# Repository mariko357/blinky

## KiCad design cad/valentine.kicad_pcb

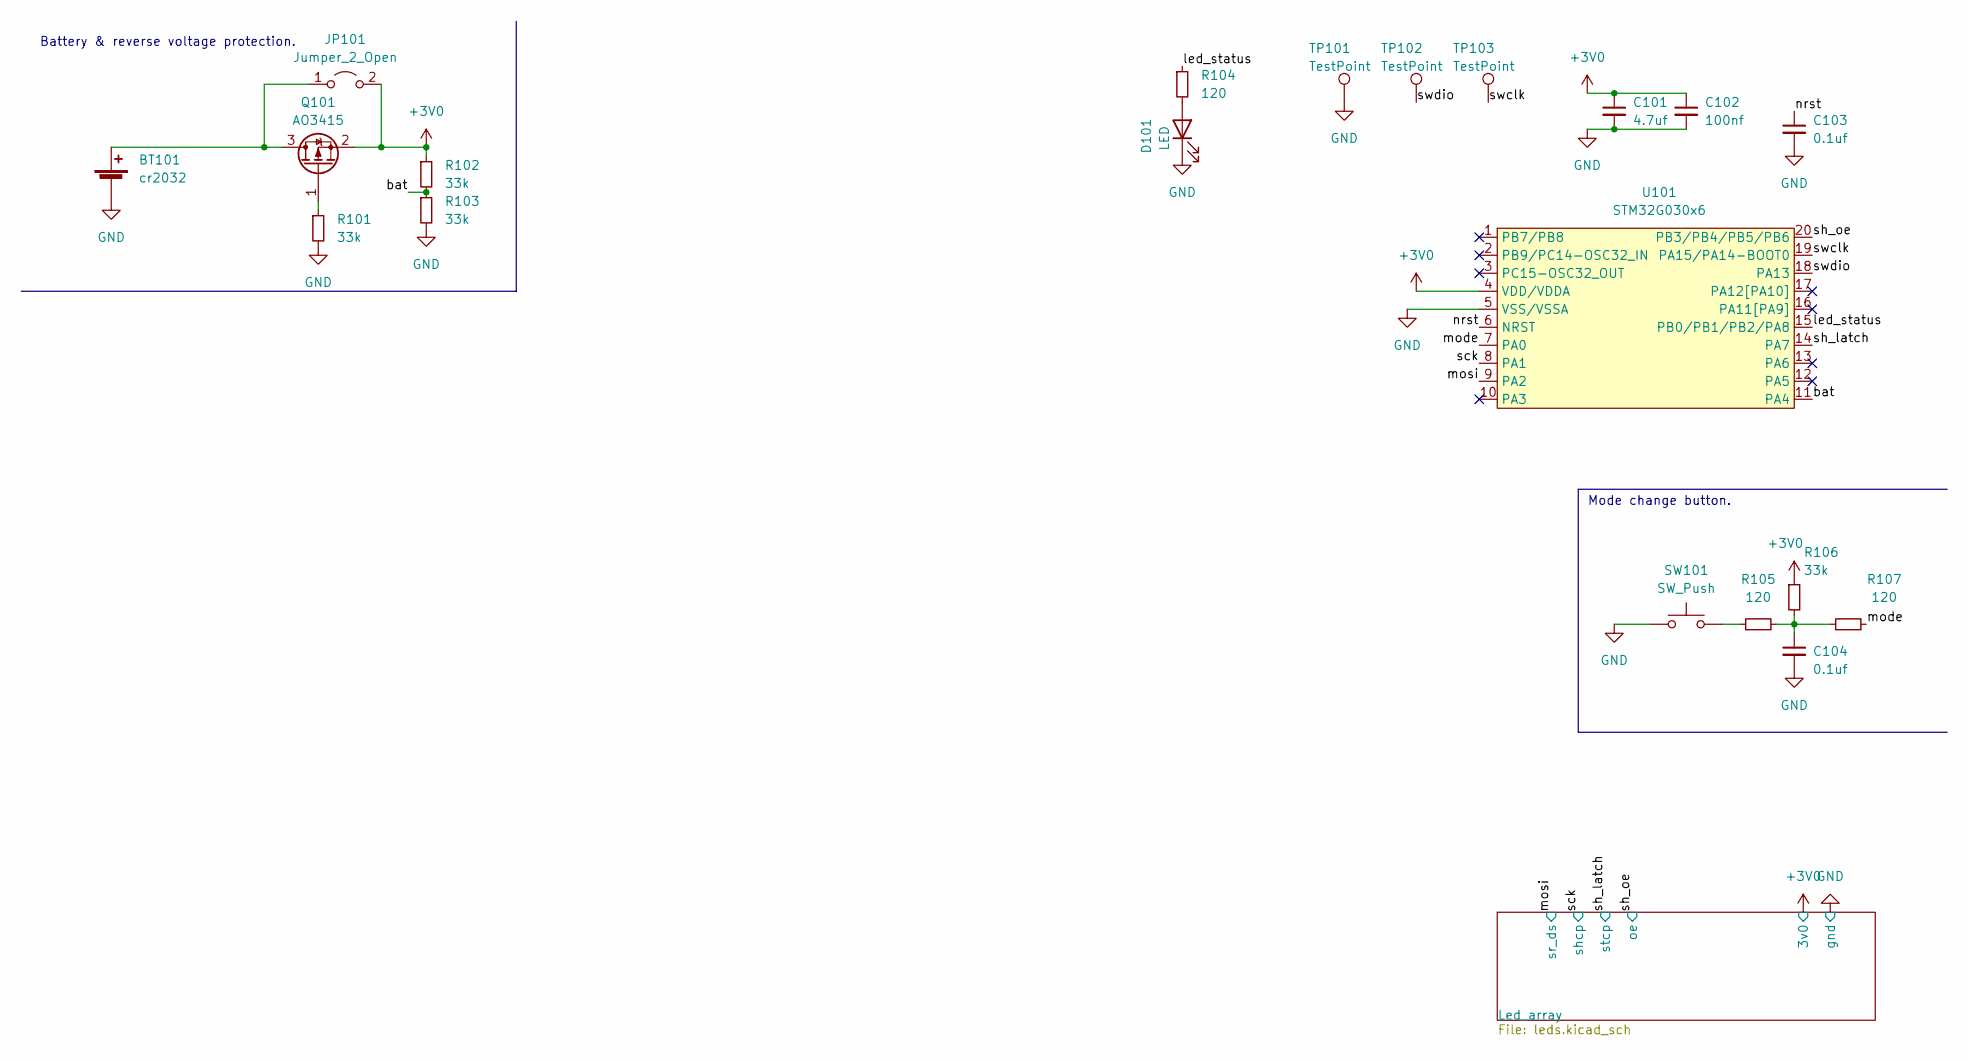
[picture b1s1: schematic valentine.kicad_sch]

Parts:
BT101: cr2032; BatteryHolder_Keystone_3002_1x2032
C101: 4.7uf; C_0603_1608Metric
C102: 100nf; C_0603_1608Metric
C103, C104: 0.1uf; C_0603_1608Metric
D101: LED; LED_0603_1608Metric
JP101: Jumper_2_Open; SolderJumper-2_P1.3mm_Open_TrianglePad1.0x1.5mm
Q101: AO3415; SOT-23
R101, R102, R103, R106: 33k; R_0603_1608Metric
R104, R105, R107: 120; R_0603_1608Metric
SW101: SW_Push; SW_SPST_TL3342
TP101, TP102, TP103: TestPoint; TestPoint_Pad_D1.5mm
U101: STM32G030x6; TSSOP-20_4.4x6.5mm_P0.65mm

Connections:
+3V0: C101.1, C102.1, JP101.2 (B), Q101.2 (S), R102.1, R106.1, U101.4 (VDD/VDDA); also elsewhere on the board
/bat: R102.2, R103.1, U101.11 (PA4)
/led_status: R104.1, U101.15 (PB0/PB1/PB2/PA8)
/mode: R107.2, U101.7 (PA0)
/mosi: U101.9 (PA2); also elsewhere on the board
/nrst: C103.1, U101.6 (NRST)
/sck: U101.8 (PA1); also elsewhere on the board
/sh_latch: U101.14 (PA7); also elsewhere on the board
/sh_oe: U101.20 (PB3/PB4/PB5/PB6); also elsewhere on the board
/swclk: TP103.1, U101.19 (PA15/PA14-BOOT0)
/swdio: TP102.1, U101.18 (PA13)
GND: BT101.2 (-), C101.2, C102.2, C103.2, C104.2, D101.1 (K), R101.2, R103.2, SW101.1, TP101.1, U101.5 (VSS/VSSA); also elsewhere on the board
unnamed: BT101.1 (+), JP101.1 (A), Q101.3 (D)
unnamed: C104.1, R105.2, R106.2, R107.1
unnamed: D101.2 (A), R104.2
unnamed: Q101.1 (G), R101.1
unnamed: R105.1, SW101.2

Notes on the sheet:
Battery & reverse voltage protection.
Mode change button.

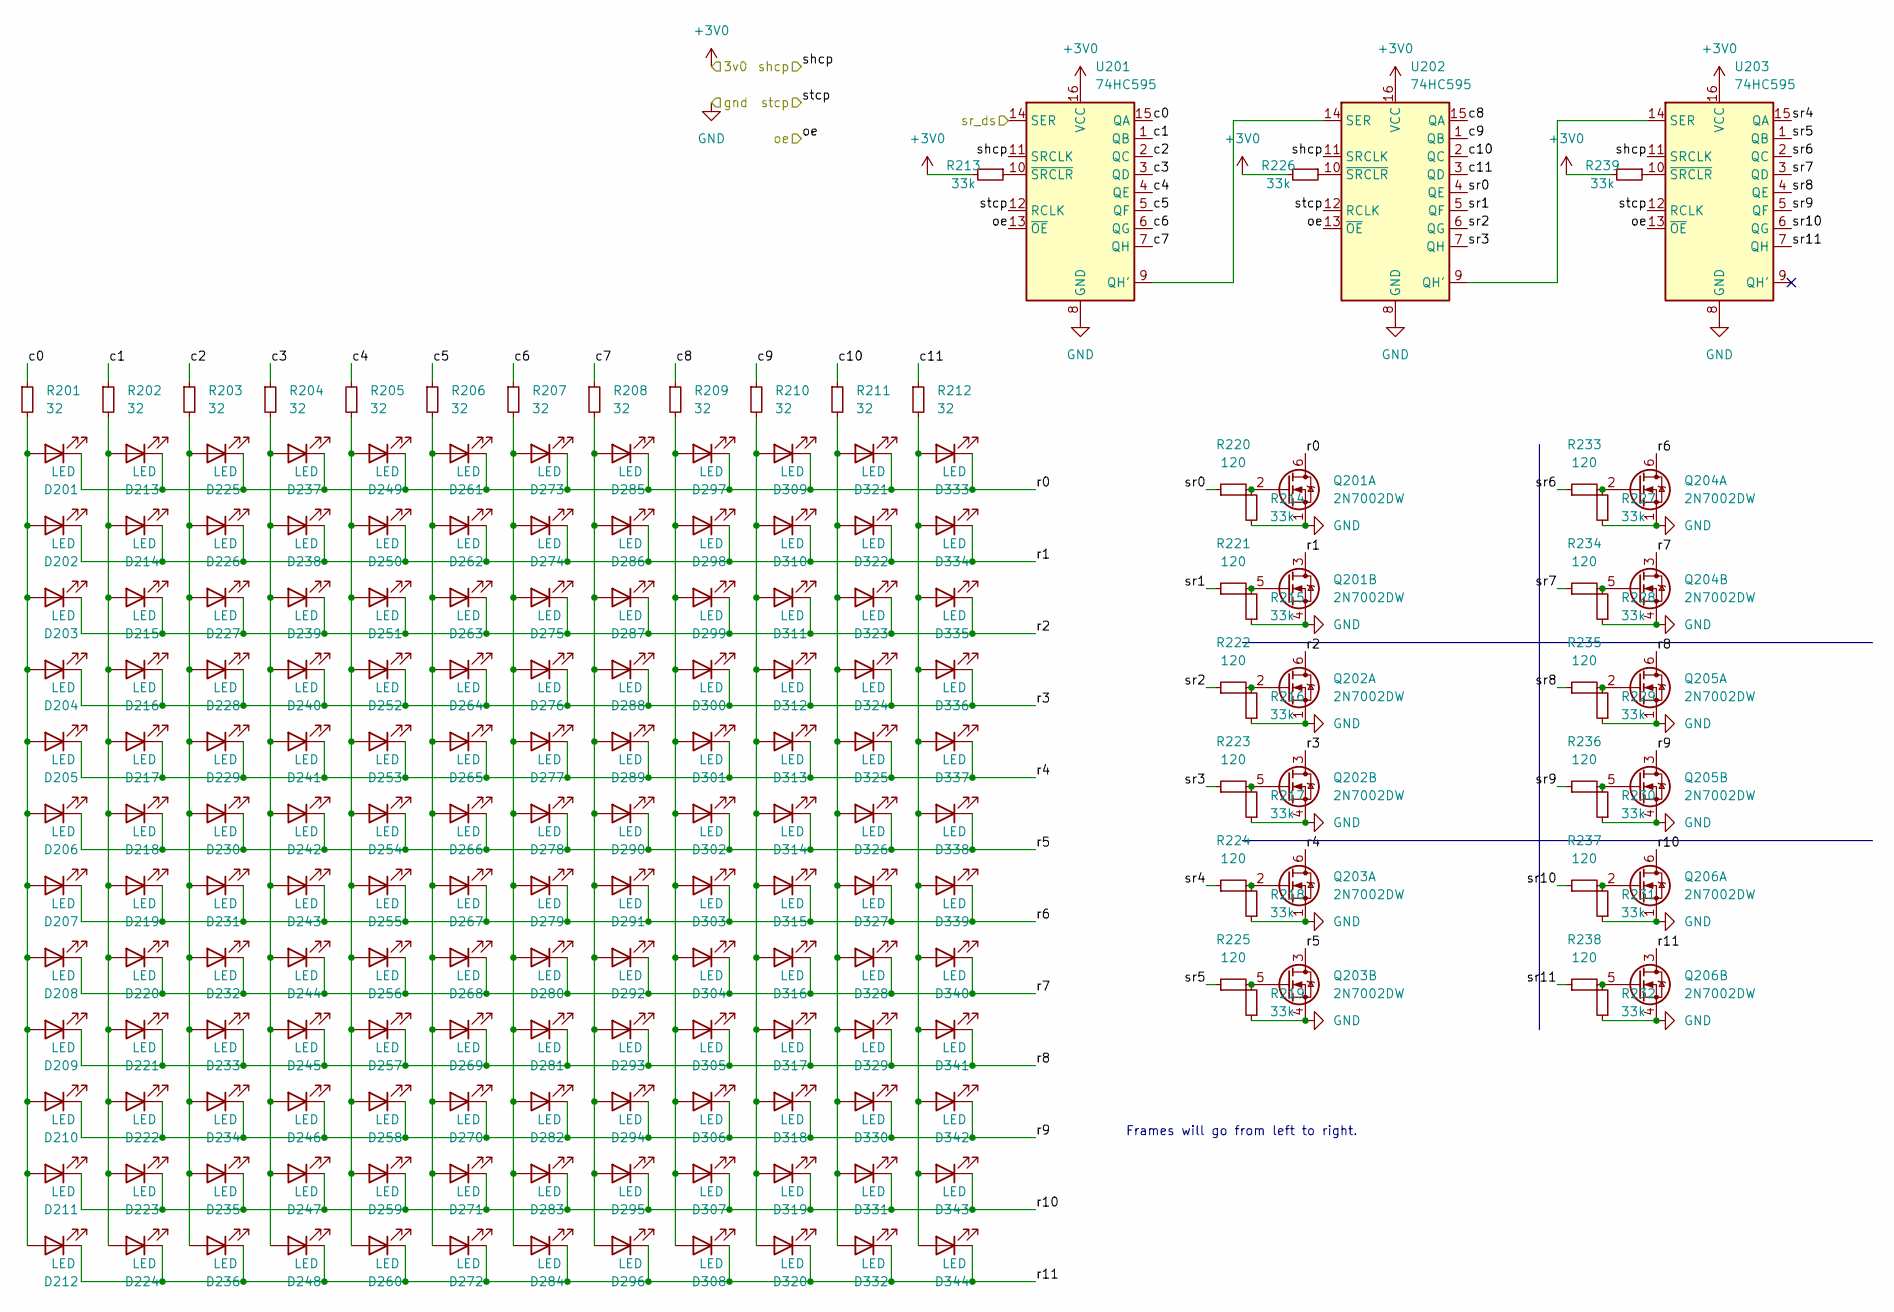
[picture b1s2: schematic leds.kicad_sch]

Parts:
D201, D202, D203, D204, D205, D206, D207, D208, D209, D210, D211, D212, D213, D214, D215, D216, D217, D218, D219, D220, D221, D222, D223, D224, D225, D226, D227, D228, D229, D230, D231, D232, D233, D234, D235, D236, D237, D238, D239, D240, D241, D242, D243, D244, D245, D246, D247, D248, D249, D250, D251, D252, D253, D254, D255, D256, D257, D258, D259, D260, D261, D262, D263, D264, D265, D266, D267, D268, D269, D270, D271, D272, D273, D274, D275, D276, D277, D278, D279, D280, D281, D282, D283, D284, D285, D286, D287, D288, D289, D290, D291, D292, D293, D294, D295, D296, D297, D298, D299, D300, D301, D302, D303, D304, D305, D306, D307, D308, D309, D310, D311, D312, D313, D314, D315, D316, D317, D318, D319, D320, D321, D322, D323, D324, D325, D326, D327, D328, D329, D330, D331, D332, D333, D334, D335, D336, D337, D338, D339, D340, D341, D342, D343, D344: LED; LED_0603_1608Metric
Q201, Q202, Q203, Q204, Q205, Q206: 2N7002DW; SOT-363_SC-70-6
R201, R202, R203, R204, R205, R206, R207, R208, R209, R210, R211, R212: 32; R_0603_1608Metric
R213, R214, R215, R216, R217, R218, R219, R226, R227, R228, R229, R230, R231, R232, R239: 33k; R_0603_1608Metric
R220, R221, R222, R223, R224, R225, R233, R234, R235, R236, R237, R238: 120; R_0603_1608Metric
U201, U202, U203: 74HC595; TSSOP-16_4.4x5mm_P0.65mm

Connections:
+3V0: R213.2, R226.2, R239.2, U201.16 (VCC), U202.16 (VCC), U203.16 (VCC); also elsewhere on the board
/Led_array/c0: R201.1, U201.15 (QA)
/Led_array/c1: R202.1, U201.1 (QB)
/Led_array/c2: R203.1, U201.2 (QC)
/Led_array/c3: R204.1, U201.3 (QD)
/Led_array/c4: R205.2, U201.4 (QE)
/Led_array/c5: R206.1, U201.5 (QF)
/Led_array/c6: R207.1, U201.6 (QG)
/Led_array/c7: R208.1, U201.7 (QH)
/Led_array/c8: R209.1, U202.15 (QA)
/Led_array/c9: R210.1, U202.1 (QB)
/Led_array/c10: R211.1, U202.2 (QC)
/Led_array/c11: R212.1, U202.3 (QD)
/Led_array/r0: D201.1 (K), D213.1 (K), D225.1 (K), D237.1 (K), D249.1 (K), D261.1 (K), D273.1 (K), D285.1 (K), D297.1 (K), D309.1 (K), D321.1 (K), D333.1 (K), Q201.6 (D)
/Led_array/r1: D202.1 (K), D214.1 (K), D226.1 (K), D238.1 (K), D250.1 (K), D262.1 (K), D274.1 (K), D286.1 (K), D298.1 (K), D310.1 (K), D322.1 (K), D334.1 (K), Q201.3 (D)
/Led_array/r2: D203.1 (K), D215.1 (K), D227.1 (K), D239.1 (K), D251.1 (K), D263.1 (K), D275.1 (K), D287.1 (K), D299.1 (K), D311.1 (K), D323.1 (K), D335.1 (K), Q202.6 (D)
/Led_array/r3: D204.1 (K), D216.1 (K), D228.1 (K), D240.1 (K), D252.1 (K), D264.1 (K), D276.1 (K), D288.1 (K), D300.1 (K), D312.1 (K), D324.1 (K), D336.1 (K), Q202.3 (D)
/Led_array/r4: D205.1 (K), D217.1 (K), D229.1 (K), D241.1 (K), D253.1 (K), D265.1 (K), D277.1 (K), D289.1 (K), D301.1 (K), D313.1 (K), D325.1 (K), D337.1 (K), Q203.6 (D)
/Led_array/r5: D206.1 (K), D218.1 (K), D230.1 (K), D242.1 (K), D254.1 (K), D266.1 (K), D278.1 (K), D290.1 (K), D302.1 (K), D314.1 (K), D326.1 (K), D338.1 (K), Q203.3 (D)
/Led_array/r6: D207.1 (K), D219.1 (K), D231.1 (K), D243.1 (K), D255.1 (K), D267.1 (K), D279.1 (K), D291.1 (K), D303.1 (K), D315.1 (K), D327.1 (K), D339.1 (K), Q204.6 (D)
/Led_array/r7: D208.1 (K), D220.1 (K), D232.1 (K), D244.1 (K), D256.1 (K), D268.1 (K), D280.1 (K), D292.1 (K), D304.1 (K), D316.1 (K), D328.1 (K), D340.1 (K), Q204.3 (D)
/Led_array/r8: D209.1 (K), D221.1 (K), D233.1 (K), D245.1 (K), D257.1 (K), D269.1 (K), D281.1 (K), D293.1 (K), D305.1 (K), D317.1 (K), D329.1 (K), D341.1 (K), Q205.6 (D)
/Led_array/r9: D210.1 (K), D222.1 (K), D234.1 (K), D246.1 (K), D258.1 (K), D270.1 (K), D282.1 (K), D294.1 (K), D306.1 (K), D318.1 (K), D330.1 (K), D342.1 (K), Q205.3 (D)
/Led_array/r10: D211.1 (K), D223.1 (K), D235.1 (K), D247.1 (K), D259.1 (K), D271.1 (K), D283.1 (K), D295.1 (K), D307.1 (K), D319.1 (K), D331.1 (K), D343.1 (K), Q206.6 (D)
/Led_array/r11: D212.1 (K), D224.1 (K), D236.1 (K), D248.1 (K), D260.1 (K), D272.1 (K), D284.1 (K), D296.1 (K), D308.1 (K), D320.1 (K), D332.1 (K), D344.1 (K), Q206.3 (D)
/Led_array/sr0: R220.1, U202.4 (QE)
/Led_array/sr1: R221.1, U202.5 (QF)
/Led_array/sr2: R222.1, U202.6 (QG)
/Led_array/sr3: R223.1, U202.7 (QH)
/Led_array/sr4: R224.1, U203.15 (QA)
/Led_array/sr5: R225.1, U203.1 (QB)
/Led_array/sr6: R233.1, U203.2 (QC)
/Led_array/sr7: R234.1, U203.3 (QD)
/Led_array/sr8: R235.1, U203.4 (QE)
/Led_array/sr9: R236.1, U203.5 (QF)
/Led_array/sr10: R237.1, U203.6 (QG)
/Led_array/sr11: R238.1, U203.7 (QH)
/mosi: U201.14 (SER); also elsewhere on the board
/sck: U201.11 (SRCLK), U202.11 (SRCLK), U203.11 (SRCLK); also elsewhere on the board
/sh_latch: U201.12 (RCLK), U202.12 (RCLK), U203.12 (RCLK); also elsewhere on the board
/sh_oe: U201.13 (~OE), U202.13 (~OE), U203.13 (~OE); also elsewhere on the board
GND: Q201.1 (S), Q201.4 (S), Q202.1 (S), Q202.4 (S), Q203.1 (S), Q203.4 (S), Q204.1 (S), Q204.4 (S), Q205.1 (S), Q205.4 (S), Q206.1 (S), Q206.4 (S), R214.2, R215.1, R216.1, R217.1, R218.1, R219.1, R227.1, R228.1, R229.1, R230.1, R231.1, R232.1, U201.8 (GND), U202.8 (GND), U203.8 (GND); also elsewhere on the board
unnamed: D201.2 (A), D202.2 (A), D203.2 (A), D204.2 (A), D205.2 (A), D206.2 (A), D207.2 (A), D208.2 (A), D209.2 (A), D210.2 (A), D211.2 (A), D212.2 (A), R201.2
unnamed: D213.2 (A), D214.2 (A), D215.2 (A), D216.2 (A), D217.2 (A), D218.2 (A), D219.2 (A), D220.2 (A), D221.2 (A), D222.2 (A), D223.2 (A), D224.2 (A), R202.2
unnamed: D225.2 (A), D226.2 (A), D227.2 (A), D228.2 (A), D229.2 (A), D230.2 (A), D231.2 (A), D232.2 (A), D233.2 (A), D234.2 (A), D235.2 (A), D236.2 (A), R203.2
unnamed: D237.2 (A), D238.2 (A), D239.2 (A), D240.2 (A), D241.2 (A), D242.2 (A), D243.2 (A), D244.2 (A), D245.2 (A), D246.2 (A), D247.2 (A), D248.2 (A), R204.2
unnamed: D249.2 (A), D250.2 (A), D251.2 (A), D252.2 (A), D253.2 (A), D254.2 (A), D255.2 (A), D256.2 (A), D257.2 (A), D258.2 (A), D259.2 (A), D260.2 (A), R205.1
unnamed: D261.2 (A), D262.2 (A), D263.2 (A), D264.2 (A), D265.2 (A), D266.2 (A), D267.2 (A), D268.2 (A), D269.2 (A), D270.2 (A), D271.2 (A), D272.2 (A), R206.2
unnamed: D273.2 (A), D274.2 (A), D275.2 (A), D276.2 (A), D277.2 (A), D278.2 (A), D279.2 (A), D280.2 (A), D281.2 (A), D282.2 (A), D283.2 (A), D284.2 (A), R207.2
unnamed: D285.2 (A), D286.2 (A), D287.2 (A), D288.2 (A), D289.2 (A), D290.2 (A), D291.2 (A), D292.2 (A), D293.2 (A), D294.2 (A), D295.2 (A), D296.2 (A), R208.2
unnamed: D297.2 (A), D298.2 (A), D299.2 (A), D300.2 (A), D301.2 (A), D302.2 (A), D303.2 (A), D304.2 (A), D305.2 (A), D306.2 (A), D307.2 (A), D308.2 (A), R209.2
unnamed: D309.2 (A), D310.2 (A), D311.2 (A), D312.2 (A), D313.2 (A), D314.2 (A), D315.2 (A), D316.2 (A), D317.2 (A), D318.2 (A), D319.2 (A), D320.2 (A), R210.2
unnamed: D321.2 (A), D322.2 (A), D323.2 (A), D324.2 (A), D325.2 (A), D326.2 (A), D327.2 (A), D328.2 (A), D329.2 (A), D330.2 (A), D331.2 (A), D332.2 (A), R211.2
unnamed: D333.2 (A), D334.2 (A), D335.2 (A), D336.2 (A), D337.2 (A), D338.2 (A), D339.2 (A), D340.2 (A), D341.2 (A), D342.2 (A), D343.2 (A), D344.2 (A), R212.2
unnamed: Q201.2 (G), R214.1, R220.2
unnamed: Q201.5 (G), R215.2, R221.2
unnamed: Q202.2 (G), R216.2, R222.2
unnamed: Q202.5 (G), R217.2, R223.2
unnamed: Q203.2 (G), R218.2, R224.2
unnamed: Q203.5 (G), R219.2, R225.2
unnamed: Q204.2 (G), R227.2, R233.2
unnamed: Q204.5 (G), R228.2, R234.2
unnamed: Q205.2 (G), R229.2, R235.2
unnamed: Q205.5 (G), R230.2, R236.2
unnamed: Q206.2 (G), R231.2, R237.2
unnamed: Q206.5 (G), R232.2, R238.2
unnamed: R213.1, U201.10 (~SRCLR)
unnamed: R226.1, U202.10 (~SRCLR)
unnamed: R239.1, U203.10 (~SRCLR)
unnamed: U201.9 (QH'), U202.14 (SER)
unnamed: U202.9 (QH'), U203.14 (SER)

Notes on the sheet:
Frames will go from left to right.

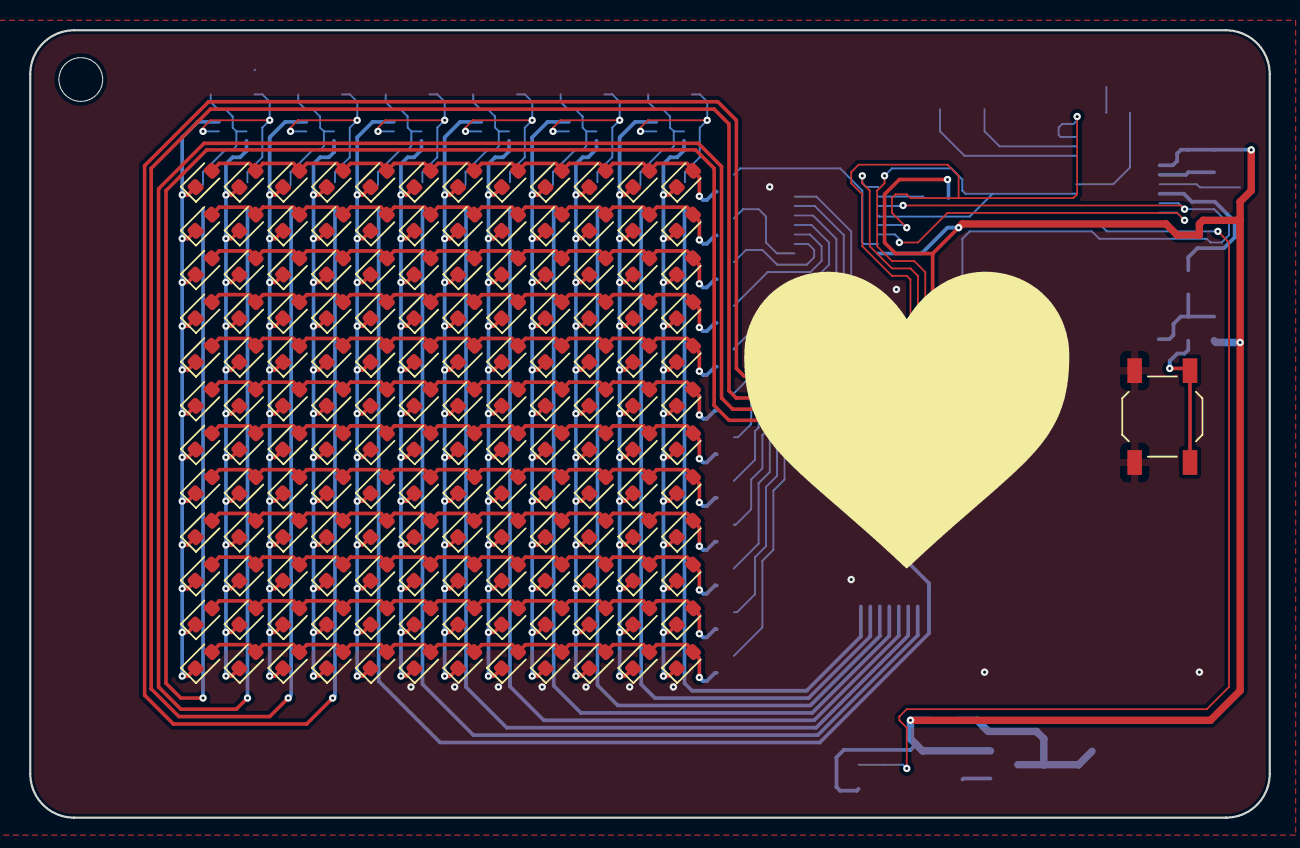
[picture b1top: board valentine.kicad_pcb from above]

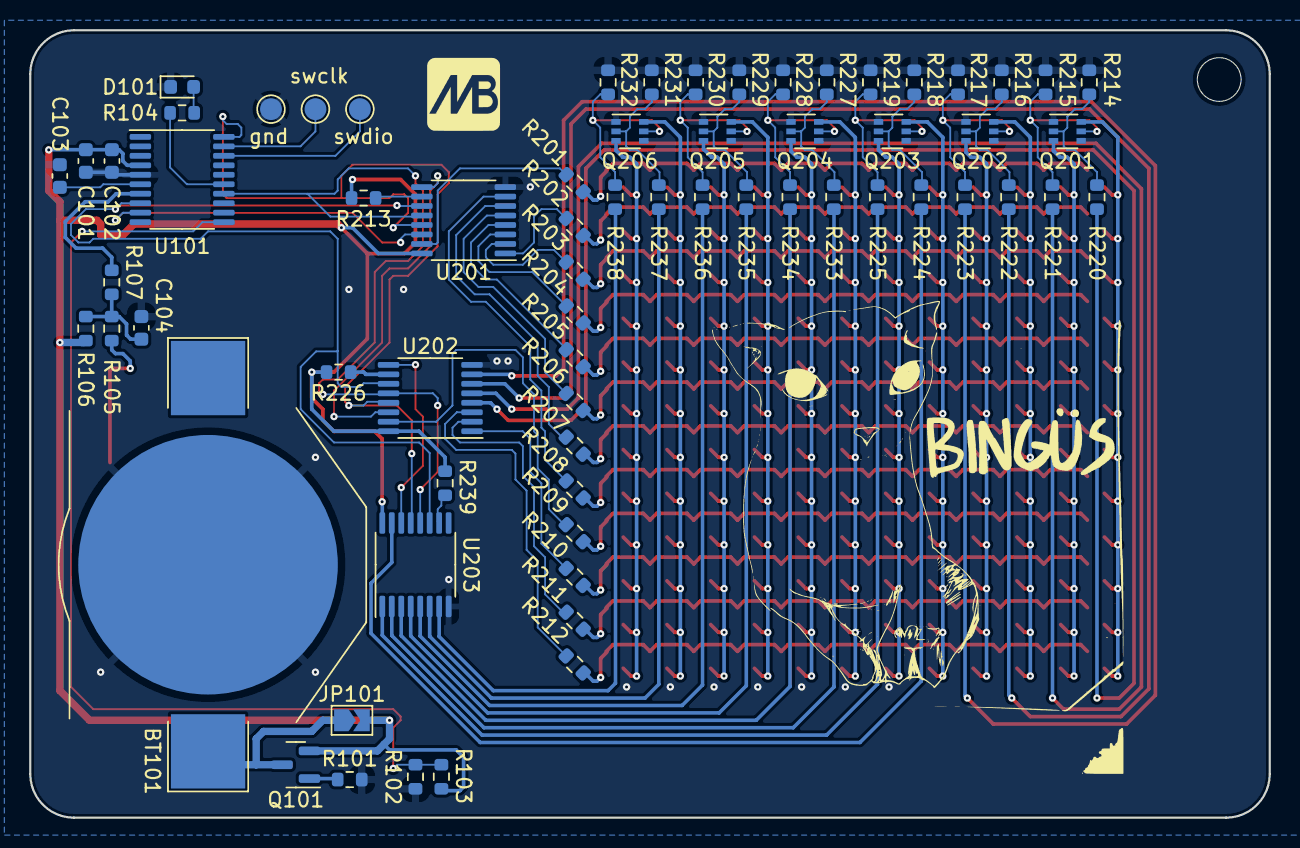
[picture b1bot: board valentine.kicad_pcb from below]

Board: 2 copper layers, 85.0 x 54.0 mm, 212 parts (67 on the bottom side), 82 nets.

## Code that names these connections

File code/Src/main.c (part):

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  /*Configure GPIO pin Output Level */
  HAL_GPIO_WritePin(GPIOB, GPIO_PIN_0|GPIO_PIN_3, GPIO_PIN_RESET);

  /*Configure GPIO pin : PA0 */
  GPIO_InitStruct.Pin = GPIO_PIN_0;
  GPIO_InitStruct.Mode = GPIO_MODE_IT_FALLING;
  GPIO_InitStruct.Pull = GPIO_NOPULL;
  HAL_GPIO_Init(GPIOA, &GPIO_InitStruct);

  /*Configure GPIO pin : PA7 */
  GPIO_InitStruct.Pin = GPIO_PIN_7;
  GPIO_InitStruct.Mode = GPIO_MODE_OUTPUT_PP;
  GPIO_InitStruct.Pull = GPIO_NOPULL;
  GPIO_InitStruct.Speed = GPIO_SPEED_FREQ_LOW;
  HAL_GPIO_Init(GPIOA, &GPIO_InitStruct);

  /*Configure GPIO pins : PB0 PB3 */
  GPIO_InitStruct.Pin = GPIO_PIN_0|GPIO_PIN_3;
  GPIO_InitStruct.Mode = GPIO_MODE_OUTPUT_PP;
  GPIO_InitStruct.Pull = GPIO_NOPULL;
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
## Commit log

2023-05-05 Initial commit.

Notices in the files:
code/Src/main.c:
Copyright (c) 2023 STMicroelectronics.
All rights reserved.
This software is licensed under terms that can be found in the LICENSE file
